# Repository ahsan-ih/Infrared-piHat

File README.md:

# ANAVI Infrared pHAT

DISCLAIMER:: The original creators of the ANAVI Infrared pHAT are [ANAVI-Technology](https://anavi.technology/). The development has been presented in the given repository just for demonstration purposes.

ANAVI Infared pHAT is an open source hardware Raspberry Pi pHAT (add-on board) for rapid prototyping of Internet of Things (IoT) powered by free and open source software. It features:

* 2x IR transmitters
* IR receiver (IR photo sensor)
* Slots for up to 3 plug and play I2C sensors for temperature, barometric pressure, humidity and light
* UART (Universal asynchronous receiver/transmitter) pins for debugging

ANAVI Infrared pHAT is available at [CrowdSupply](https://www.crowdsupply.com/anavi-technology/infrared-phat).

# License

The project is released under the [Creative Commons Attribution-ShareAlike 4.0 International (CC BY-SA 4.0)](https://creativecommons.org/licenses/by-sa/4.0/).

Note: This is a human-readable summary of (and not a substitute for) the [license](https://creativecommons.org/licenses/by-sa/4.0/legalcode).

You are free to:(does this work?)

Share — copy and redistribute the material in any medium or format Adapt — remix, transform, and build upon the material for any purpose, even commercially. The licensor cannot revoke these freedoms as long as you follow the license terms. Under the following terms:

Attribution — You must give appropriate credit, provide a link to the license, and indicate if changes were made. You may do so in any reasonable manner, but not in any way that suggests the licensor endorses you or your use. ShareAlike — If you remix, transform, or build upon the material, you must distribute your contributions under the same license as the original. No additional restrictions — You may not apply legal terms or technological measures that legally restrict others from doing anything the license permits. Notices:

You do not have to comply with the license for elements of the material in the public domain or where your use is permitted by an applicable exception or limitation. No warranties are given. The license may not give you all of the permissions necessary for your intended use. For example, other rights such as publicity, privacy, or moral rights may limit how you use the material.

You will have to provide a link to the original creator of the project http://www.anavi.technology on any documentation or website.

Credit can be attributed through a link to the creator website: http://www.anavi.technology

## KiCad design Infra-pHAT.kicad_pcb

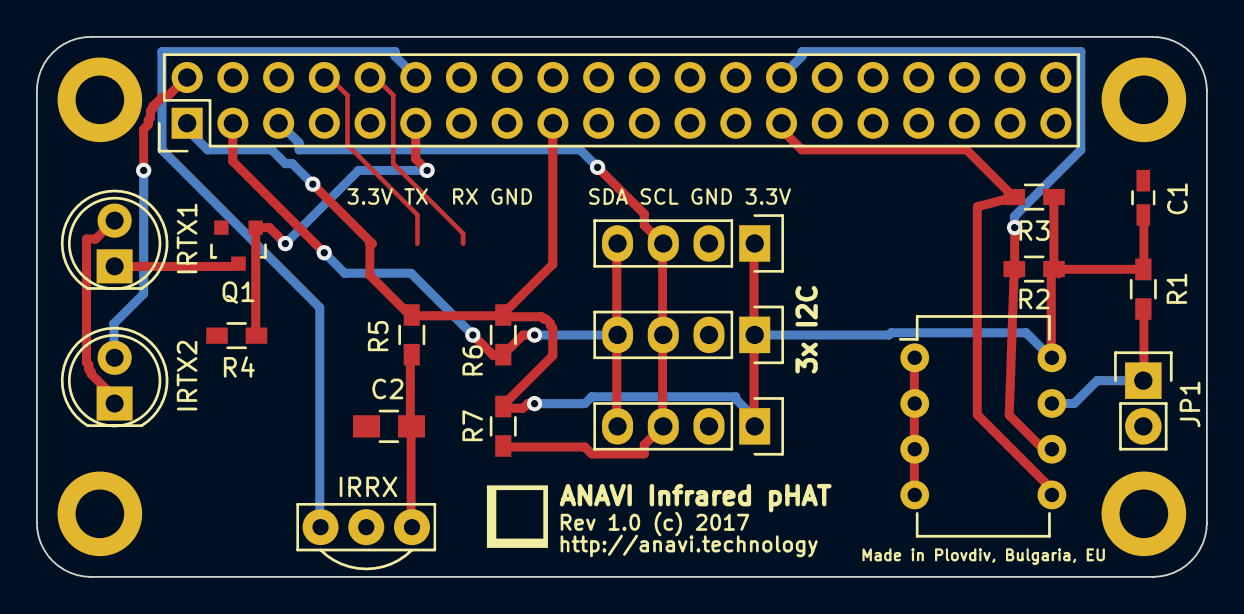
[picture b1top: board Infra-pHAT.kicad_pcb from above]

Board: 2 copper layers, 65.0 x 30.0 mm, 23 parts (0 on the bottom side), 13 nets.

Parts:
C1: 0.1; C_0603_HandSoldering
C2: 4.7; C_0805_HandSoldering
IRRX: TSOP34838; TSOP38X
IRTX1, IRTX2: L-53F3BT; LED-5MM
JP1: JUMPER; Pin_Header_Straight_1x02
Q1: BC817; SOT-23
R1: 1K; R_0603_HandSoldering
R2, R3, R6, R7: 4.7K; R_0603_HandSoldering
R4: 10K; R_0603_HandSoldering
R5: 470; R_0603_HandSoldering
RASP_CONN1: Raspberry_PI; Pin_Header_Straight_2x20
REF1, REF2, REF3, REF4: MountingHole_2.7mm_M2.5_DIN965_Pad
SENS1, SENS2, SENS3: I2C_SENS_1; Pin_Header_Straight_1x04
U1: CAT24C32WI-GT3; DIP-8_W7.62mm

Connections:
+3V3: C1.1, R1.1, R2.1, R3.1, R5.1, R6.1, R7.1, RASP_CONN1.1, RASP_CONN1.17, SENS1.1, SENS2.1, SENS3.1, U1.8
+5V: IRTX2.2, RASP_CONN1.2, RASP_CONN1.4
GND: C1.2, C2.2, IRRX.2, JP1.2, Q1.2, R4.1, RASP_CONN1.6, RASP_CONN1.9, RASP_CONN1.14, RASP_CONN1.20, RASP_CONN1.25, RASP_CONN1.30, RASP_CONN1.34, RASP_CONN1.39, SENS1.2, SENS2.2, SENS3.2, U1.1, U1.2, U1.3, U1.4
unnamed: C2.1, IRRX.3, R5.2
unnamed: IRRX.1, RASP_CONN1.12
unnamed: IRTX1.1, Q1.3
unnamed: IRTX1.2, IRTX2.1
unnamed: JP1.1, R1.2, U1.7
unnamed: Q1.1, R4.2, RASP_CONN1.11
unnamed: R2.2, RASP_CONN1.28, U1.6
unnamed: R3.2, RASP_CONN1.27, U1.5
unnamed: R6.2, RASP_CONN1.3, SENS1.4, SENS2.4, SENS3.4
unnamed: R7.2, RASP_CONN1.5, SENS1.3, SENS2.3, SENS3.3

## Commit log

2020-03-30 not my first commit
2020-03-30 diff
2020-03-30 reverting to not my first commit

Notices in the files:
Infra-pHAT.kicad_pcb:
Rev 1.0 (c) 2017
